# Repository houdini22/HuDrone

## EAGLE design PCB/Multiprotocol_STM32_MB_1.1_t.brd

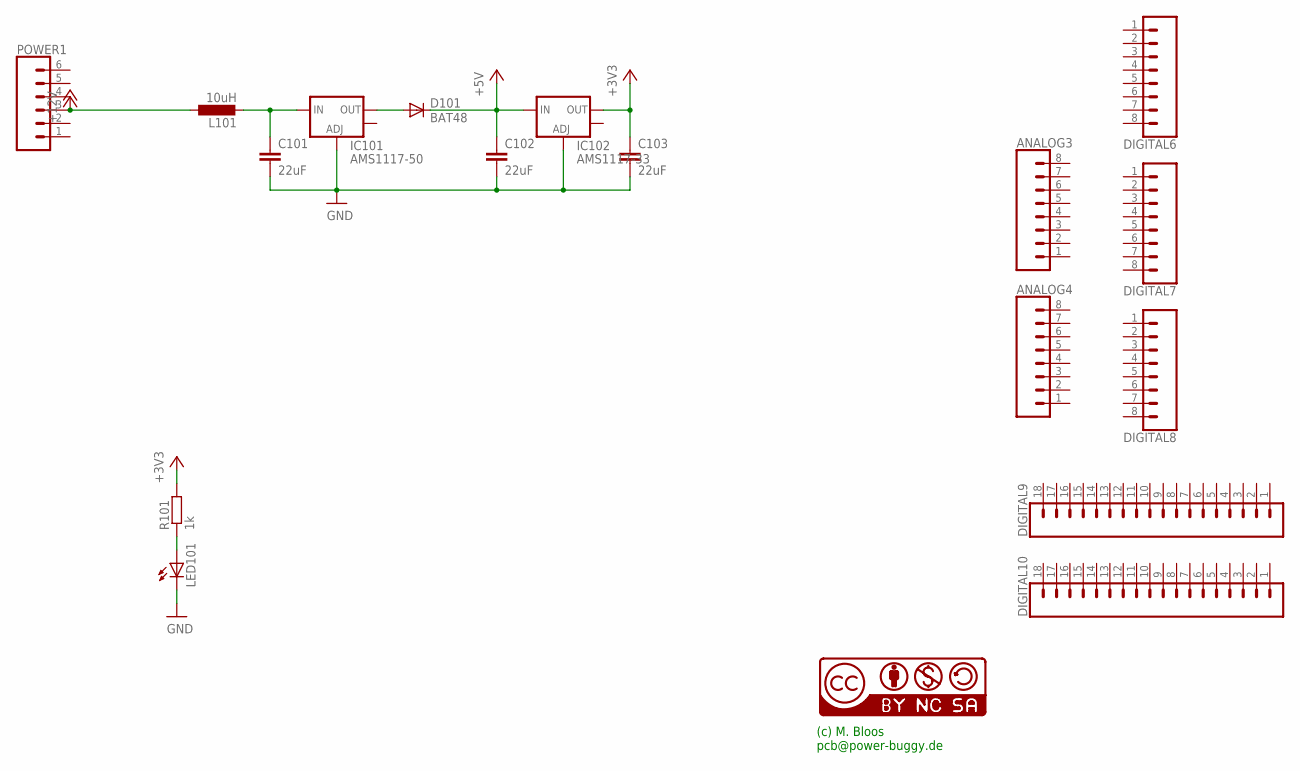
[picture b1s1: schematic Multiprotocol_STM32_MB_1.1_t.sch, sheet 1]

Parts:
ANALOG3, ANALOG4: CONN_08NO_SILK_FEMALE_PTH; 1X08_NO_SILK
C101, C102, C103: 22uF; C1210K
D101: BAT48; MINIMELF
DIGITAL6, DIGITAL7, DIGITAL8: CONN_08NO_SILK_FEMALE_PTH; 1X08_NO_SILK
DIGITAL9, DIGITAL10: CONN_18; 1X18
IC101: AMS1117-50; SOT223
IC102: AMS1117-33; SOT223
L101: 10uH; L1812
LED101: LED3MM
NIX101: CC-NC-BCNIX; CC-NC-B_NIX
POWER1: CONN_06NO_SILK_FEMALE_PTH; 1X06_NO_SILK
R101: 1k; R0805

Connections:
+3V3: C103.1, IC102.2 (OUT), R101.2; also elsewhere on the board
+5V: C102.1, D101.C, IC102.3 (IN); also elsewhere on the board
+12V: L101.1, POWER1.3; also elsewhere on the board
GND: C101.2, C102.2, C103.2, IC101.1 (ADJ), IC102.1 (ADJ), LED101.K (C); also elsewhere on the board
unnamed: C101.1, IC101.3 (IN), L101.2
unnamed: LED101.A, R101.1
unnamed: D101.A, IC101.2 (OUT)

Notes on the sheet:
(c) M. Bloos pcb@power-buggy.de

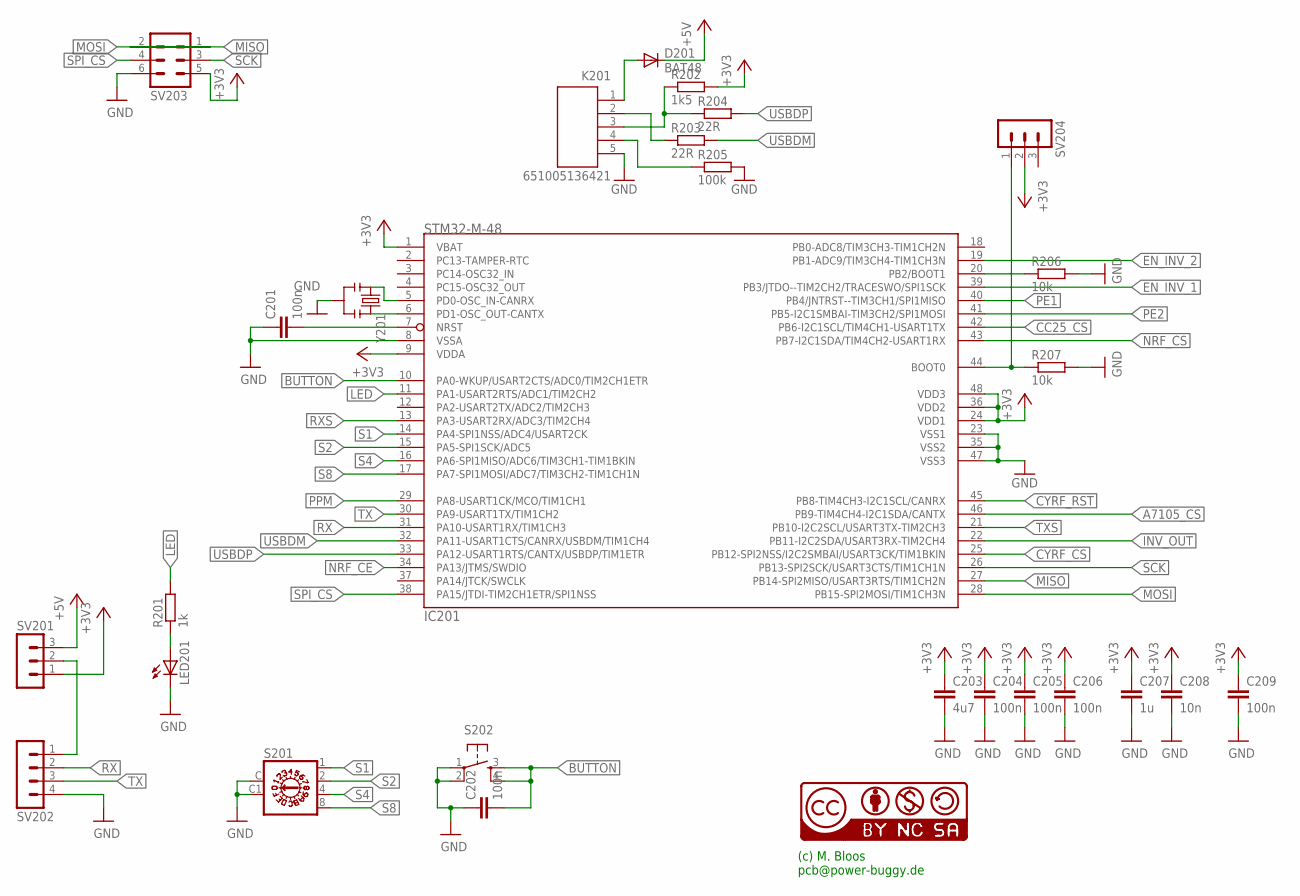
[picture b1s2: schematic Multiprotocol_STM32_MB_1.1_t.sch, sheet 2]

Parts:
C201, C202, C204, C205, C206, C209: 100n; C0805
C203: 4u7; C0805
C207: 1u; C0805
C208: 10n; C0805
D201: BAT48; MINIMELF
IC201: STM32-M-48; LQFP48
K201: 651005136421
LED201: LED3MM
NIX201: CC-NC-BCNIX; CC-NC-B_NIX
R201: 1k; R0805
R202: 1k5; R0805
R203, R204: 22R; R0805
R205: 100k; R0805
R206, R207: 10k; R0805
S201: A1353HEX
S202: TAC_SWITCHPTH; TACTILE-PTH
SV201, SV204: MA03-1
SV202: MA04-1
SV203: MA03-2
Y201: CSTCE8M00G52-R0; RESONATOR-SMD

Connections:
+3V3: C203.1, C204.1, C205.1, C206.1, C207.1, C208.1, C209.1, IC201.1 (VBAT), IC201.9 (VDDA), IC201.24 (VDD1), IC201.36 (VDD2), IC201.48 (VDD3), R202.2, SV201.1, SV203.5, SV204.2; also elsewhere on the board
+5V: D201.C, SV201.3; also elsewhere on the board
A7105_CS: IC201.46 (PB9-TIM4CH4-I2C1SDA/CANTX); also elsewhere on the board
BUTTON: C202.2, IC201.10 (PA0-WKUP/USART2CTS/ADC0/TIM2CH1ETR), S202.3, S202.4
CC25_CS: IC201.42 (PB6-I2C1SCL/TIM4CH1-USART1TX); also elsewhere on the board
CYRF_CS: IC201.25 (PB12-SPI2NSS/I2C2SMBAI/USART3CK/TIM1BKIN); also elsewhere on the board
CYRF_RST: IC201.45 (PB8-TIM4CH3-I2C1SCL/CANRX); also elsewhere on the board
EN_INV_1: IC201.39 (PB3/JTDO--TIM2CH2/TRACESWO/SPI1SCK); also elsewhere on the board
EN_INV_2: IC201.19 (PB1-ADC9/TIM3CH4-TIM1CH3N); also elsewhere on the board
GND: C201.1, C202.1, C203.2, C204.2, C205.2, C206.2, C207.2, C208.2, C209.2, IC201.8 (VSSA), IC201.23 (VSS1), IC201.35 (VSS2), IC201.47 (VSS3), K201.5, LED201.K (C), R205.2, R206.2, R207.2, S201.C, S201.C1 (NC), S202.1, S202.2, SV202.4, SV203.6, Y201.2; also elsewhere on the board
INV_OUT: IC201.22 (PB11-I2C2SDA/USART3RX-TIM2CH4); also elsewhere on the board
LED: IC201.11 (PA1-USART2RTS/ADC1/TIM2CH2), R201.2
MISO: IC201.27 (PB14-SPI2MISO/USART3RTS/TIM1CH2N), SV203.2; also elsewhere on the board
MOSI: IC201.28 (PB15-SPI2MOSI/TIM1CH3N), SV203.1; also elsewhere on the board
unnamed: IC201.5 (PD0-OSC_IN-CANRX), Y201.1
unnamed: IC201.6 (PD1-OSC_OUT-CANTX), Y201.3
unnamed: SV201.2, SV202.1
unnamed: K201.4, R205.1
unnamed: LED201.A, R201.1
unnamed: C201.2, IC201.7 (NRST)
unnamed: K201.3, R202.1, R204.1
unnamed: D201.A, K201.1
unnamed: K201.2, R203.1
unnamed: IC201.44 (BOOT0), R207.1, SV204.1
unnamed: IC201.20 (PB2/BOOT1), R206.1
NRF_CE: IC201.34 (PA13/JTMS/SWDIO); also elsewhere on the board
NRF_CS: IC201.43 (PB7-I2C1SDA/TIM4CH2-USART1RX); also elsewhere on the board
PE1: IC201.40 (PB4/JNTRST--TIM3CH1/SPI1MISO); also elsewhere on the board
PE2: IC201.41 (PB5-I2C1SMBAI-TIM3CH2/SPI1MOSI); also elsewhere on the board
PPM: IC201.29 (PA8-USART1CK/MCO/TIM1CH1); also elsewhere on the board
RX: IC201.31 (PA10-USART1RX/TIM1CH3), SV202.2
RXS: IC201.13 (PA3-USART2RX/ADC3/TIM2CH4); also elsewhere on the board
S1: IC201.14 (PA4-SPI1NSS/ADC4/USART2CK), S201.1
S2: IC201.15 (PA5-SPI1SCK/ADC5), S201.2
S4: IC201.16 (PA6-SPI1MISO/ADC6/TIM3CH1-TIM1BKIN), S201.4
S8: IC201.17 (PA7-SPI1MOSI/ADC7/TIM3CH2-TIM1CH1N), S201.8
SCK: IC201.26 (PB13-SPI2SCK/USART3CTS/TIM1CH1N), SV203.3; also elsewhere on the board
SPI_CS: IC201.38 (PA15/JTDI-TIM2CH1ETR/SPI1NSS), SV203.4
TX: IC201.30 (PA9-USART1TX/TIM1CH2), SV202.3
TXS: IC201.21 (PB10-I2C2SCL/USART3TX-TIM2CH3); also elsewhere on the board
USBDM: IC201.32 (PA11-USART1CTS/CANRX/USBDM/TIM1CH4), R203.2
USBDP: IC201.33 (PA12-USART1RTS/CANTX/USBDP/TIM1ETR), R204.2

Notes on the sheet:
(c) M. Bloos pcb@power-buggy.de

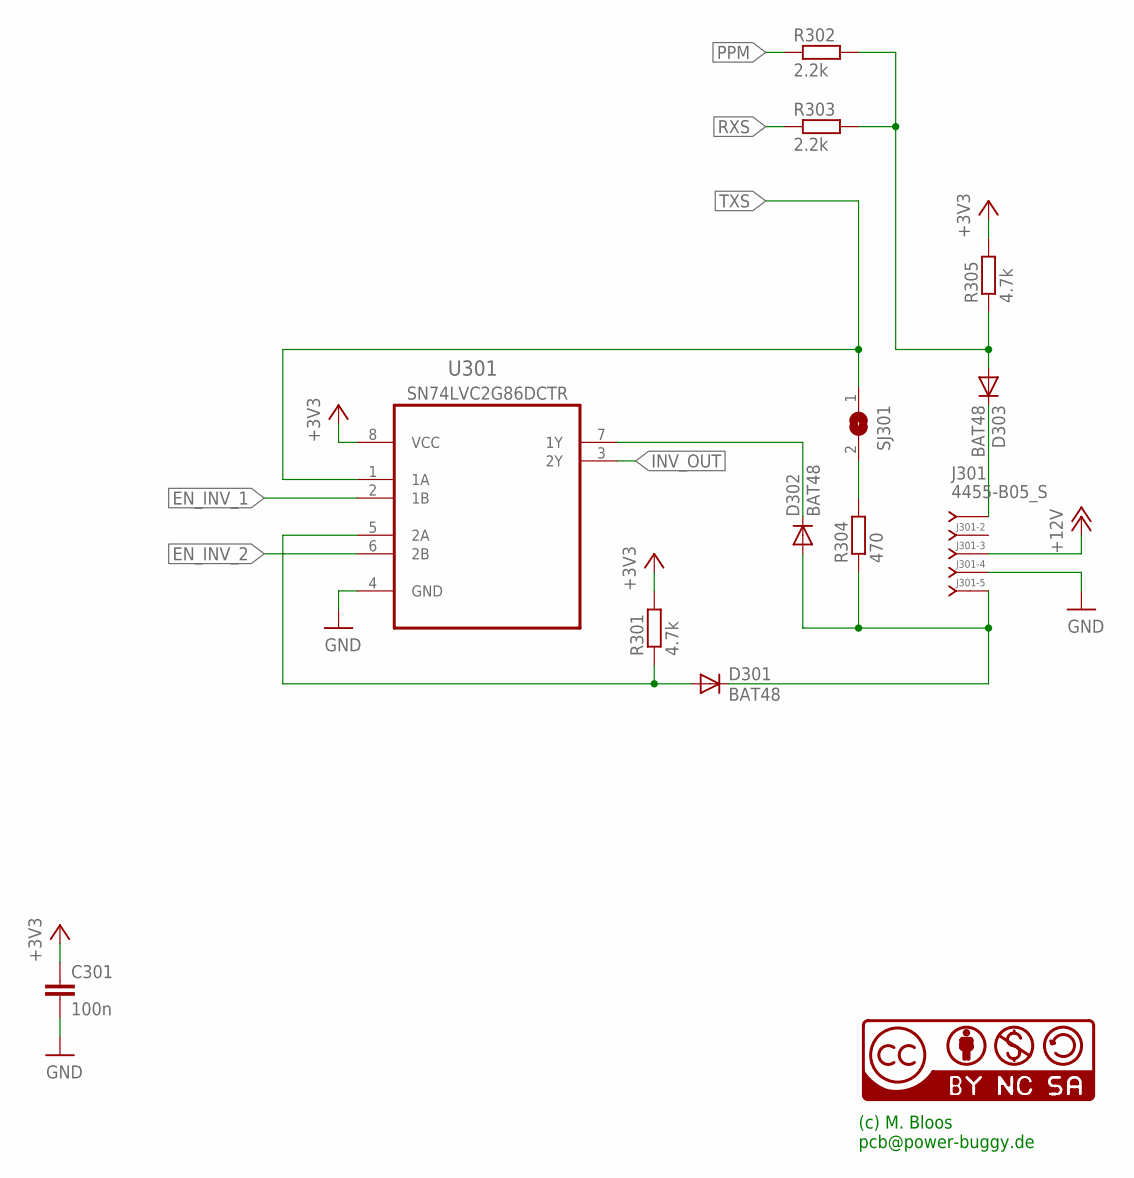
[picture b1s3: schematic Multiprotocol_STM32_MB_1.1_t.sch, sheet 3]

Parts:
C301: 100n; C0805
D301, D302, D303: BAT48; MINIMELF
J301: 4455-B05_S; 4455-B05
NIX301: CC-NC-BCNIX; CC-NC-B_NIX
R301, R305: 4.7k; R0805
R302, R303: 2.2k; R0805
R304: 470; R0805
SJ301: SJ
U301: SN74LVC2G00DCTR; SOP65P400X130-8N

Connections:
+3V3: C301.1, R301.2, R305.2, U301.8 (VCC); also elsewhere on the board
+12V: J301.3; also elsewhere on the board
EN_INV_1: U301.2 (1B); also elsewhere on the board
EN_INV_2: U301.6 (2B); also elsewhere on the board
GND: C301.2, J301.4, U301.4 (GND); also elsewhere on the board
INV_OUT: U301.3 (2Y); also elsewhere on the board
unnamed: D302.C, U301.7 (1Y)
unnamed: R304.2, SJ301.2
unnamed: D301.A, R301.1, U301.5 (2A)
unnamed: D301.C, D302.A, J301.5, R304.1
unnamed: D303.A, R302.2, R303.2, R305.1
unnamed: D303.C, J301.1
PPM: R302.1; also elsewhere on the board
RXS: R303.1; also elsewhere on the board
TXS: SJ301.1, U301.1 (1A); also elsewhere on the board

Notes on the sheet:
SN74LVC2G86DCTR
(c) M. Bloos pcb@power-buggy.de

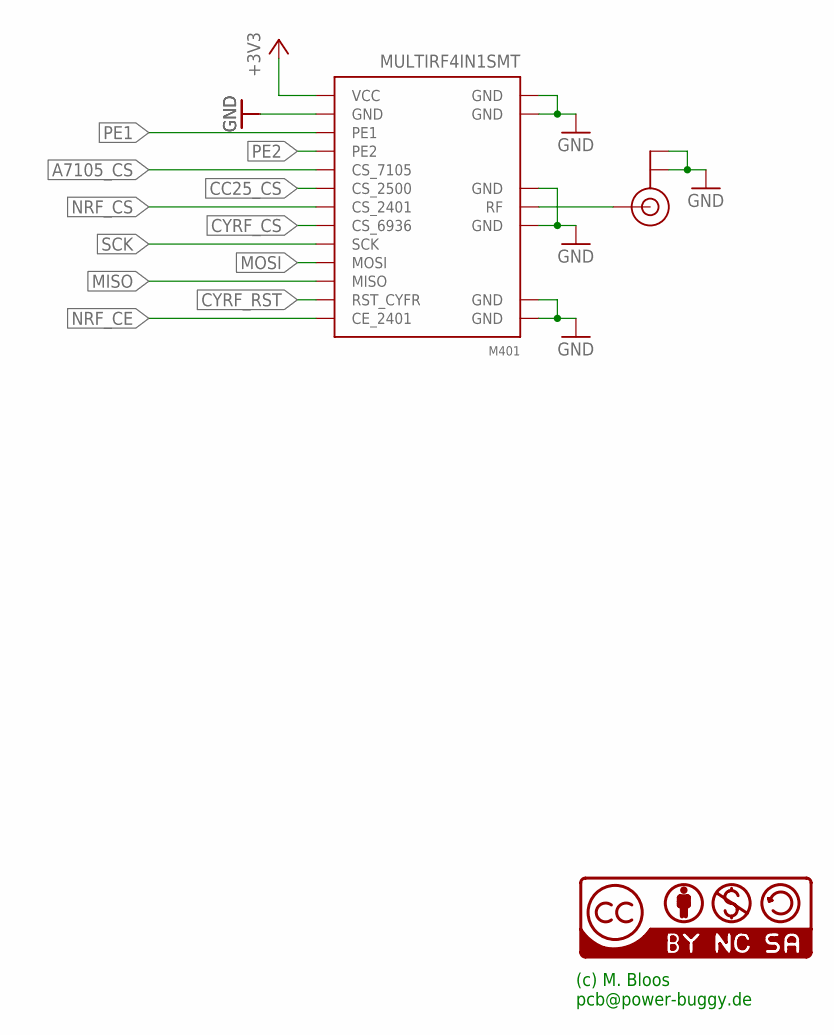
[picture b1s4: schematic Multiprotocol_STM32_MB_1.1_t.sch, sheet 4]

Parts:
CON401: U.FL
M401: MULTIRF4IN1SMT; MULTIRF4IN1-SMT
NIX401: CC-NC-BCNIX; CC-NC-B_NIX

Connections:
+3V3: M401.VCC; also elsewhere on the board
A7105_CS: M401.CS_7105; also elsewhere on the board
CC25_CS: M401.CS_2500; also elsewhere on the board
CYRF_CS: M401.CS_6936; also elsewhere on the board
CYRF_RST: M401.RST_CYFR; also elsewhere on the board
GND: CON401.P$1 (GND), CON401.P$2 (GND), M401.GND, M401.GND@1 (GND), M401.GND@2 (GND), M401.GND@3 (GND), M401.GND@4 (GND), M401.GND@5 (GND), M401.GND@6 (GND); also elsewhere on the board
MISO: M401.MISO; also elsewhere on the board
MOSI: M401.MOSI; also elsewhere on the board
unnamed: CON401.P$3 (SIGNAL), M401.RF
NRF_CE: M401.CE_2401; also elsewhere on the board
NRF_CS: M401.CS_2401; also elsewhere on the board
PE1: M401.PE1; also elsewhere on the board
PE2: M401.PE2; also elsewhere on the board
SCK: M401.SCK; also elsewhere on the board

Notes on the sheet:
(c) M. Bloos pcb@power-buggy.de

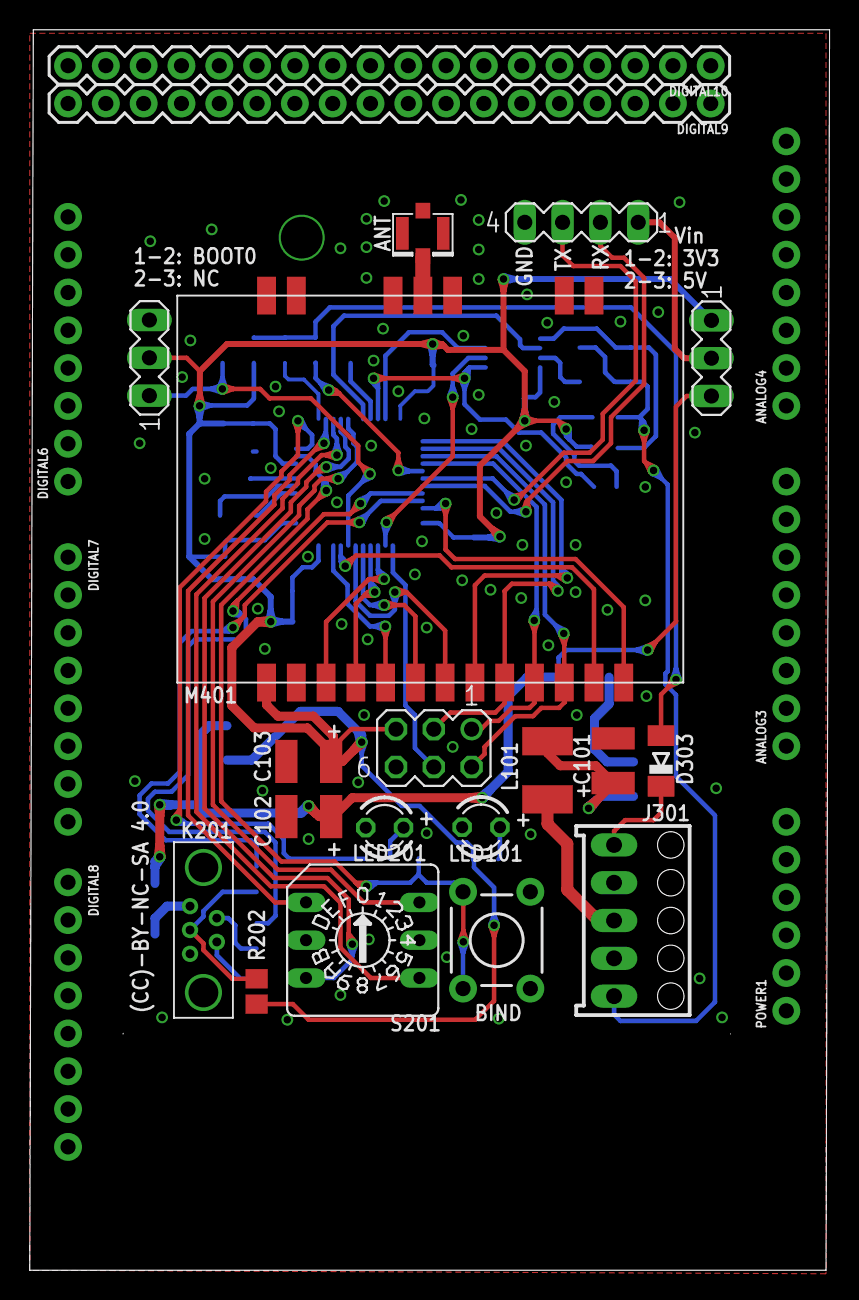
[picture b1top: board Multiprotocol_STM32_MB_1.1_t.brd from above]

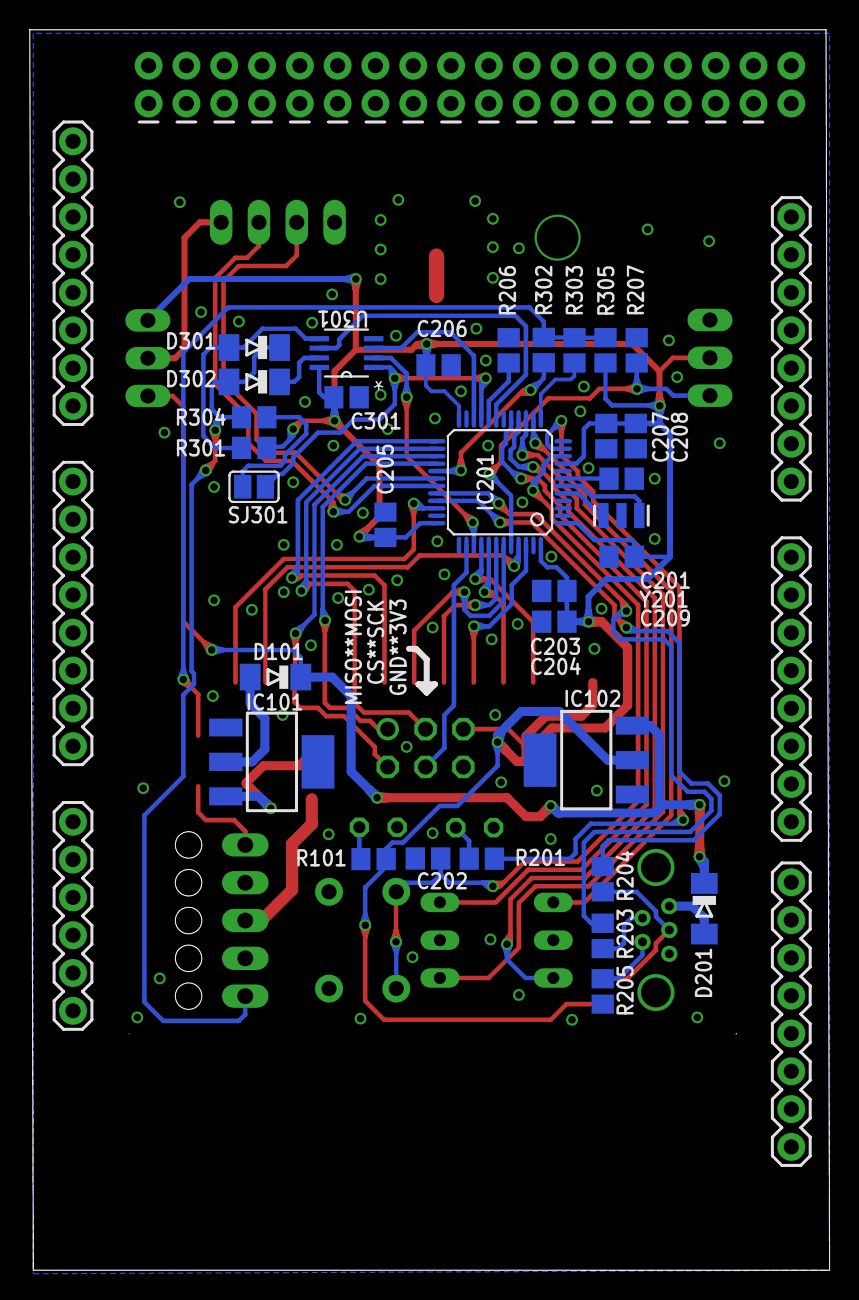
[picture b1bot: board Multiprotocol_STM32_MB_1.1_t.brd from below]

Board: 2 copper layers, 53.7 x 83.3 mm, 62 parts (32 on the bottom side), 53 nets.

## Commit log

2019-10-26 desktop app boilerplate
2019-10-26 app maximized
2019-10-26 EAGLE added
2019-10-27 config, serial port vendor lip
2019-10-27 wizard
2019-10-27 serial
2019-10-27 serial ok (TODO: cipher)
2019-10-27 serial page6
2019-10-27 wizard setup
2019-10-27 create profile 1
2019-10-28 profiles
2019-10-28 profiles, wizard
2019-10-28 upload
2019-10-28 clean up
2019-10-28 menu
2019-10-28 edit
2019-10-28 edit profile
2019-10-28 remove
2019-10-31 dialog fly
2019-11-03 import
2019-11-03 linux compile ok
2019-11-09 serialport
2019-11-09 serial combo
2019-11-12 gamepad0
2019-11-12 gamepad fly radio
2019-11-14 sending
2019-11-14 steering
2019-11-15 signals
2019-11-15 connected
2019-11-15 fix send
2019-11-18 tide
2019-11-18 timers
2019-11-19 sending fixes
2019-11-20 send
2019-11-21 arduino
2019-12-01 arming
2019-12-15 arming disarming
2019-12-16 aring
2019-12-28 not working, steps
2020-01-06 cleanflight
2021-11-17 updated arduino
2021-11-17 added images
2021-11-17 removed build

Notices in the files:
parts and their libraries:
SparkFun-FreqCtrl: Licensing: CC v3.0 Share-Alike You are welcome to use this library for commercial purposes.
SparkFun-PowerIC: Licensing: Creative Commons ShareAlike 4.0 International - https://creativecommons.org/licenses/by-sa/4.0
con-molex-kk: Copyright (C) 2010, Bob Starr
